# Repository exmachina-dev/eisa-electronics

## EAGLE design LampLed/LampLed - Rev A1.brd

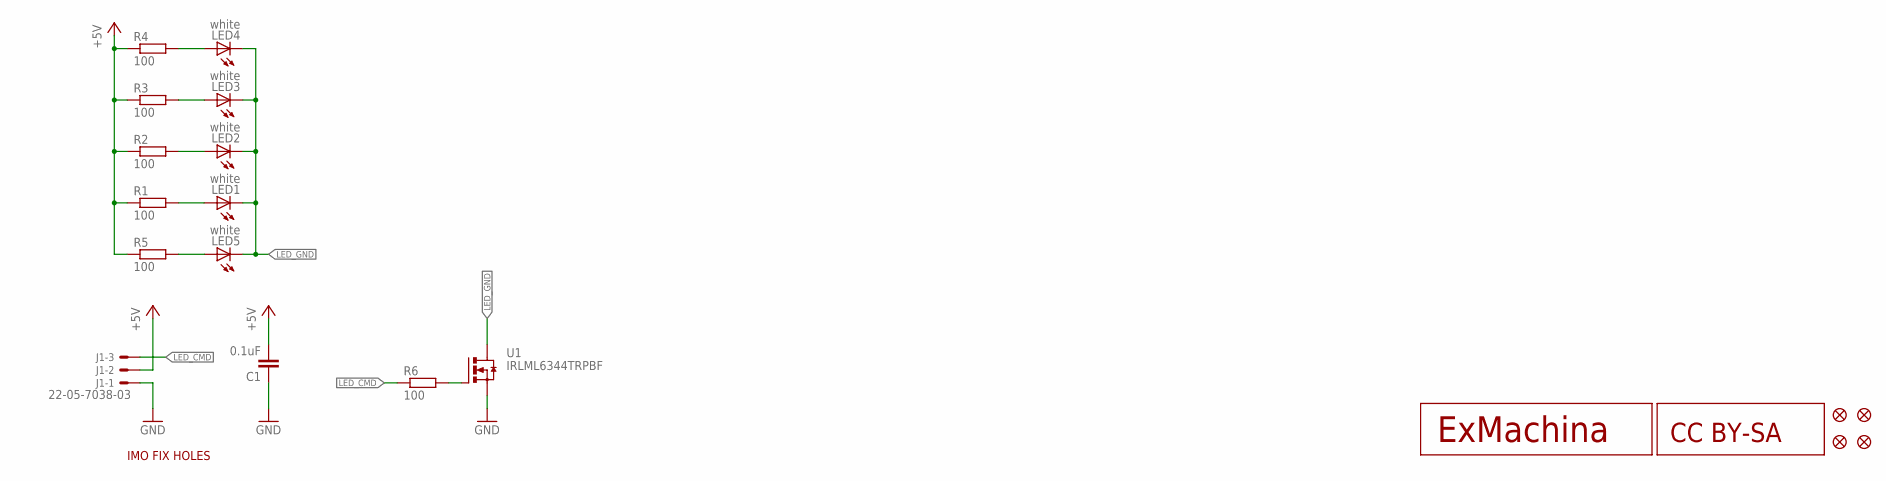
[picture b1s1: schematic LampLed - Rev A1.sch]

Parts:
C1: 0.1uF; C0603
J1: 22-05-7038-03; 7395-03
JP1, JP2, JP3, JP4: FIDUCIAL1X2; FIDUCIAL-1X2
LED1, LED2, LED3, LED4, LED5: white; CHIP-LED0603
R1, R2, R3, R4, R5, R6: 100; R0603
U1: IRLML6344TRPBF; SOT95P240X112-3N
U$1: IMO-FIXHOLES
U$2: EXMACHINA-LOGO-NAME; EXM-LOGO-BASELINE
U$3: CC-BY-SA

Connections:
+5V: C1.2, J1.2, R1.1, R2.1, R3.1, R4.1, R5.1
GND: C1.1, J1.1, U1.2 (S)
LED_CMD: J1.3, R6.1
LED_GND: LED1.C, LED2.C, LED3.C, LED4.C, LED5.C, U1.3 (D)
unnamed: LED1.A, R1.2
unnamed: LED2.A, R2.2
unnamed: LED3.A, R3.2
unnamed: LED4.A, R4.2
unnamed: LED5.A, R5.2
unnamed: R6.2, U1.1 (G)

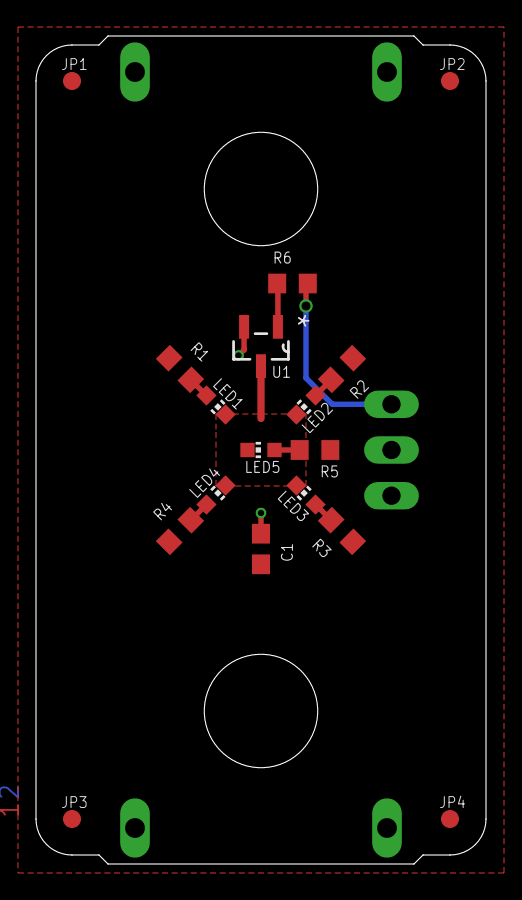
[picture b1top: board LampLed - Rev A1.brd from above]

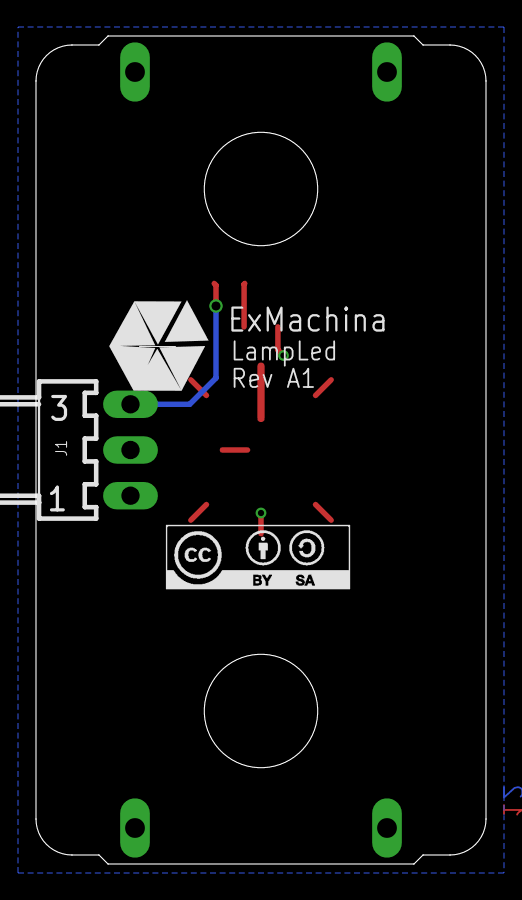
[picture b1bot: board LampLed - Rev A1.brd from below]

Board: 2 copper layers, 25.0 x 46.0 mm, 21 parts (3 on the bottom side), 10 nets.

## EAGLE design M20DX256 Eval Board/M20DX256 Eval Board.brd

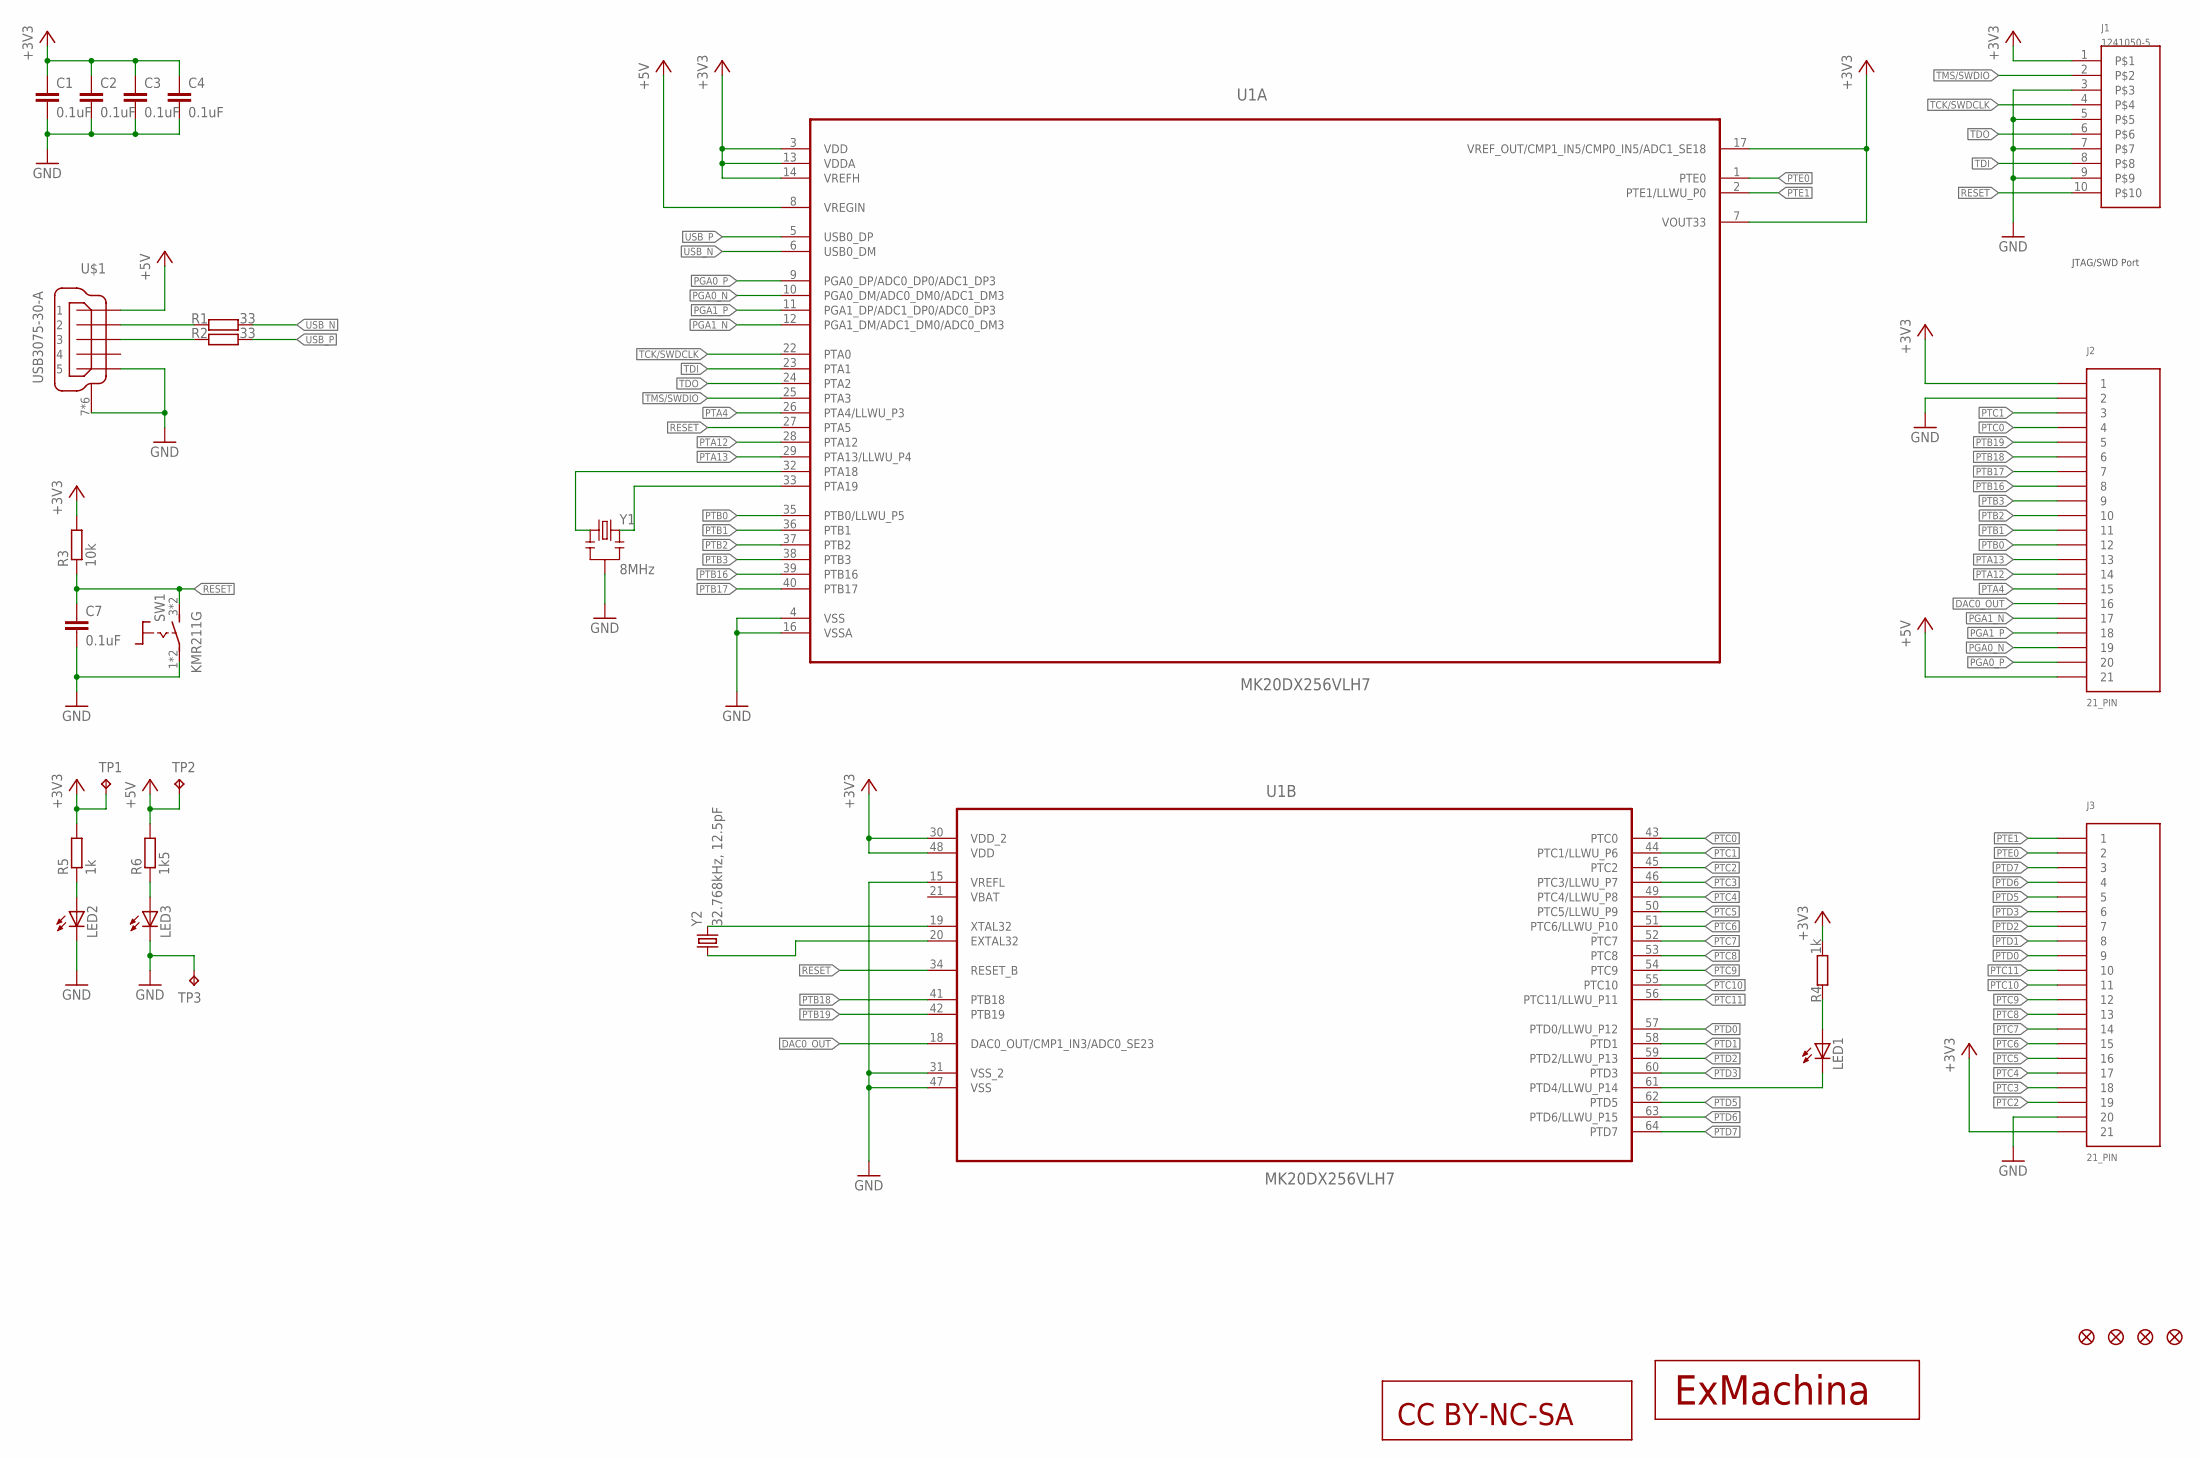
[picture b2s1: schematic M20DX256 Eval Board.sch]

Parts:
C1, C2, C3, C4, C7: 0.1uF; C0603; MPN MC0603B104K160CT
J1: 1241050-5; 2.54/2X5; MPN 1241050-5
J2, J3: 21_PIN; 21_CUSTOM
JP1, JP2, JP3, JP4: FIDUCIAL1X2; FIDUCIAL-1X2
LED1, LED2, LED3: LEDCHIP-LED0603; CHIP-LED0603
R1, R2: 33; R0603; MPN MCMR06X33R0FTL
R3: 10k; R0603; MPN MCMR06X1002FTL
R4, R5: 1k; R0603; MPN MCMR06X1001FTL
R6: 1k5; R0603; MPN MCMR06X1501FTL
SW1: KMR211G; KM_SERIE; MPN KMR211G LFS
TP1, TP2, TP3: TPB1,27; B1,27
U1: MK20DX256VLH7; QFP50P1200X1200X160-64N
U$1: USB3075-30-A; USB_MICROB_SMT; MPN USB3075-30-A
U$3: EXMACHINA-LOGO-NAME; EXM-LOGO-BASELINE
U$4: CC-BY-NC-SA
Y1: 8MHz; RESONATOR-SMD; MPN CSTCE8M00G55Z-R0
Y2: 32.768kHz, 12.5pF; ABS07; MPN ABS07-32.768KHZ-1-T

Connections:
+3V3: C1.1, C2.1, C3.1, C4.1, J1.1, J2.P$1 (1), J3.P$21 (21), R3.2, R4.2, R5.2, TP1.TP, U1.3 (VDD), U1.7 (VOUT33), U1.13 (VDDA), U1.14 (VREFH), U1.17 (VREF_OUT/CMP1_IN5/CMP0_IN5/ADC1_SE18), U1.30 (VDD_2), U1.48 (VDD)
+5V: J2.P$21 (21), R6.2, TP2.TP, U1.8 (VREGIN), U$1.1
DAC0_OUT: J2.P$16 (16), U1.18 (DAC0_OUT/CMP1_IN3/ADC0_SE23)
GND: C1.2, C2.2, C3.2, C4.2, C7.2, J1.3, J1.5, J1.7, J1.9, J2.P$2 (2), J3.P$20 (20), LED2.C, LED3.C, SW1.1 (2), SW1.2, TP3.TP, U1.4 (VSS), U1.15 (VREFL), U1.16 (VSSA), U1.31 (VSS_2), U1.47 (VSS), U$1.5, U$1.7 (S), U$1.8 (S), U$1.9 (S), U$1.10 (S), U$1.11 (S), U$1.12 (S), Y1.2
unnamed: R1.1, U$1.2
unnamed: R2.1, U$1.3
unnamed: U1.33 (PTA19), Y1.3
unnamed: U1.32 (PTA18), Y1.1
unnamed: U1.19 (XTAL32), Y2.2
unnamed: U1.20 (EXTAL32), Y2.1
unnamed: LED1.C, U1.61 (PTD4/LLWU_P14)
unnamed: LED1.A, R4.1
unnamed: LED3.A, R6.1
unnamed: LED2.A, R5.1
PGA0_N: J2.P$19 (19), U1.10 (PGA0_DM/ADC0_DM0/ADC1_DM3)
PGA0_P: J2.P$20 (20), U1.9 (PGA0_DP/ADC0_DP0/ADC1_DP3)
PGA1_N: J2.P$17 (17), U1.12 (PGA1_DM/ADC1_DM0/ADC0_DM3)
PGA1_P: J2.P$18 (18), U1.11 (PGA1_DP/ADC1_DP0/ADC0_DP3)
PTA4: J2.P$15 (15), U1.26 (PTA4/LLWU_P3)
PTA12: J2.P$14 (14), U1.28 (PTA12)
PTA13: J2.P$13 (13), U1.29 (PTA13/LLWU_P4)
PTB0: J2.P$12 (12), U1.35 (PTB0/LLWU_P5)
PTB1: J2.P$11 (11), U1.36 (PTB1)
PTB2: J2.P$10 (10), U1.37 (PTB2)
PTB3: J2.P$9 (9), U1.38 (PTB3)
PTB16: J2.P$8 (8), U1.39 (PTB16)
PTB17: J2.P$7 (7), U1.40 (PTB17)
PTB18: J2.P$6 (6), U1.41 (PTB18)
PTB19: J2.P$5 (5), U1.42 (PTB19)
PTC0: J2.P$4 (4), U1.43 (PTC0)
PTC1: J2.P$3 (3), U1.44 (PTC1/LLWU_P6)
PTC2: J3.P$19 (19), U1.45 (PTC2)
PTC3: J3.P$18 (18), U1.46 (PTC3/LLWU_P7)
PTC4: J3.P$17 (17), U1.49 (PTC4/LLWU_P8)
PTC5: J3.P$16 (16), U1.50 (PTC5/LLWU_P9)
PTC6: J3.P$15 (15), U1.51 (PTC6/LLWU_P10)
PTC7: J3.P$14 (14), U1.52 (PTC7)
PTC8: J3.P$13 (13), U1.53 (PTC8)
PTC9: J3.P$12 (12), U1.54 (PTC9)
PTC10: J3.P$11 (11), U1.55 (PTC10)
PTC11: J3.P$10 (10), U1.56 (PTC11/LLWU_P11)
PTD0: J3.P$9 (9), U1.57 (PTD0/LLWU_P12)
PTD1: J3.P$8 (8), U1.58 (PTD1)
PTD2: J3.P$7 (7), U1.59 (PTD2/LLWU_P13)
PTD3: J3.P$6 (6), U1.60 (PTD3)
PTD5: J3.P$5 (5), U1.62 (PTD5)
PTD6: J3.P$4 (4), U1.63 (PTD6/LLWU_P15)
PTD7: J3.P$3 (3), U1.64 (PTD7)
PTE0: J3.P$2 (2), U1.1 (PTE0)
PTE1: J3.P$1 (1), U1.2 (PTE1/LLWU_P0)
RESET: C7.1, J1.10, R3.1, SW1.3 (1), SW1.4 (1), U1.27 (PTA5), U1.34 (RESET_B)
TCK/SWDCLK: J1.4, U1.22 (PTA0)
TDI: J1.8, U1.23 (PTA1)
TDO: J1.6, U1.24 (PTA2)
TMS/SWDIO: J1.2, U1.25 (PTA3)
USB_N: R1.2, U1.6 (USB0_DM)
USB_P: R2.2, U1.5 (USB0_DP)
VBAT: U1.21 (VBAT)

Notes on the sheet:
JTAG/SWD Port

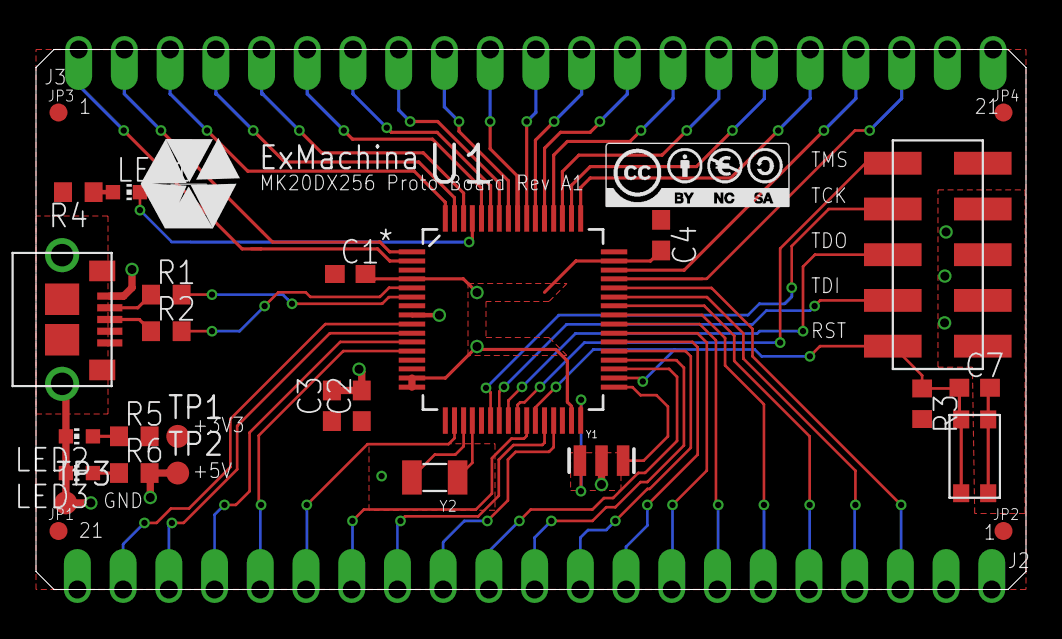
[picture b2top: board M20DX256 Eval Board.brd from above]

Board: 2 copper layers, 55.0 x 30.0 mm, 31 parts (0 on the bottom side), 57 nets.

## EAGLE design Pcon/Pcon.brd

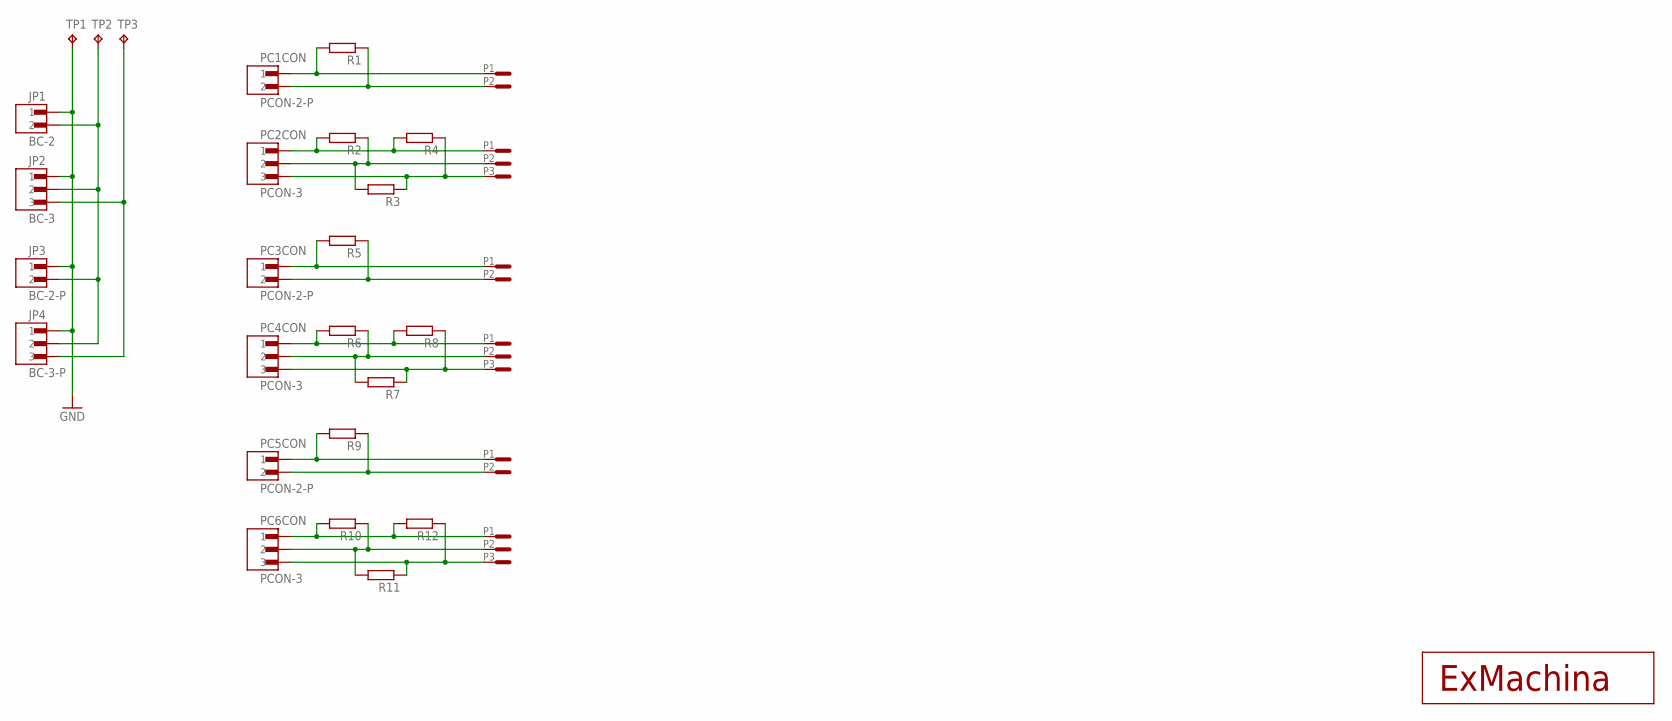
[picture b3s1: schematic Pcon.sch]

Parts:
JP1: BC-2
JP2: BC-3
JP3: BC-2-P
JP4: BC-3-P
PC1, PC3, PC5: PCON-2-P; PCON-2
PC2, PC4, PC6: PCON-3
R1, R2, R3, R4, R5, R6, R7, R8, R9, R10, R11, R12: R-EU_R0603; R0603
TP1, TP2, TP3: TPB1,27; B1,27
U$1: EXMACHINA-LOGO; EXM-LOGO

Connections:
GND: JP1.1, JP2.1, JP3.1, JP4.1, TP1.TP
unnamed: PC1.2, PC1.P2, R1.1
unnamed: PC1.1, PC1.P1, R1.2
unnamed: PC2.3, PC2.P3, R3.1, R4.1
unnamed: PC2.2, PC2.P2, R2.1, R3.2
unnamed: PC2.1, PC2.P1, R2.2, R4.2
unnamed: JP1.2, JP2.2, JP3.2, JP4.2, TP2.TP
unnamed: JP2.3, JP4.3, TP3.TP
unnamed: PC3.2, PC3.P2, R5.1
unnamed: PC3.1, PC3.P1, R5.2
unnamed: PC4.3, PC4.P3, R7.1, R8.1
unnamed: PC4.2, PC4.P2, R6.1, R7.2
unnamed: PC4.1, PC4.P1, R6.2, R8.2
unnamed: PC5.2, PC5.P2, R9.1
unnamed: PC5.1, PC5.P1, R9.2
unnamed: PC6.3, PC6.P3, R11.1, R12.1
unnamed: PC6.2, PC6.P2, R10.1, R11.2
unnamed: PC6.1, PC6.P1, R10.2, R12.2

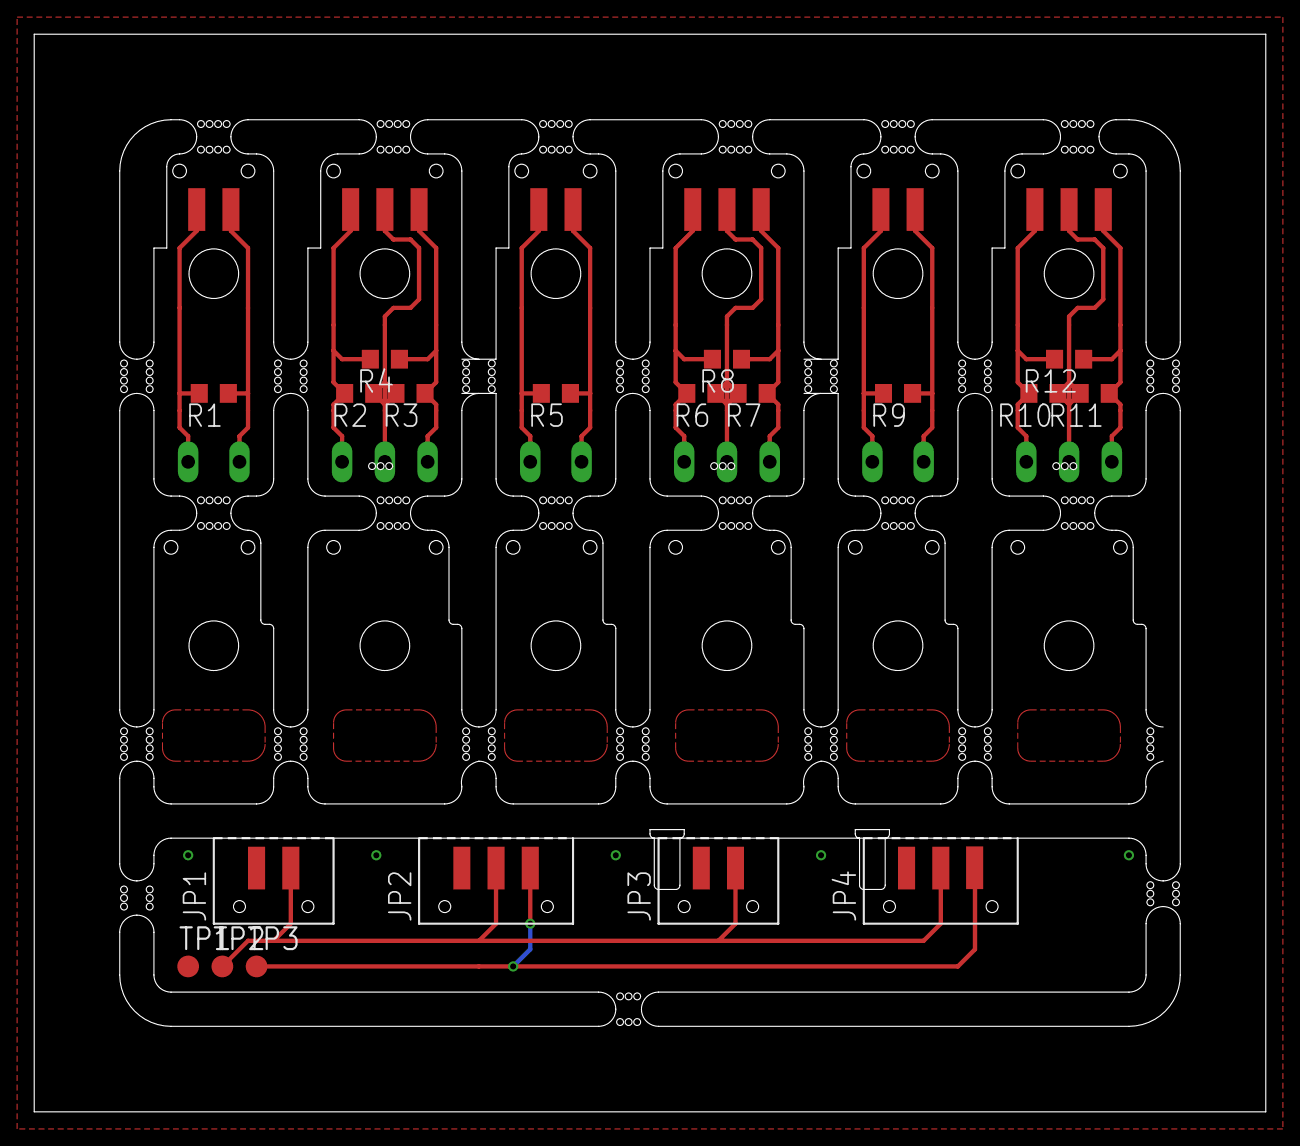
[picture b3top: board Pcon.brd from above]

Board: 2 copper layers, 72.0 x 63.0 mm, 26 parts (1 on the bottom side), 18 nets.

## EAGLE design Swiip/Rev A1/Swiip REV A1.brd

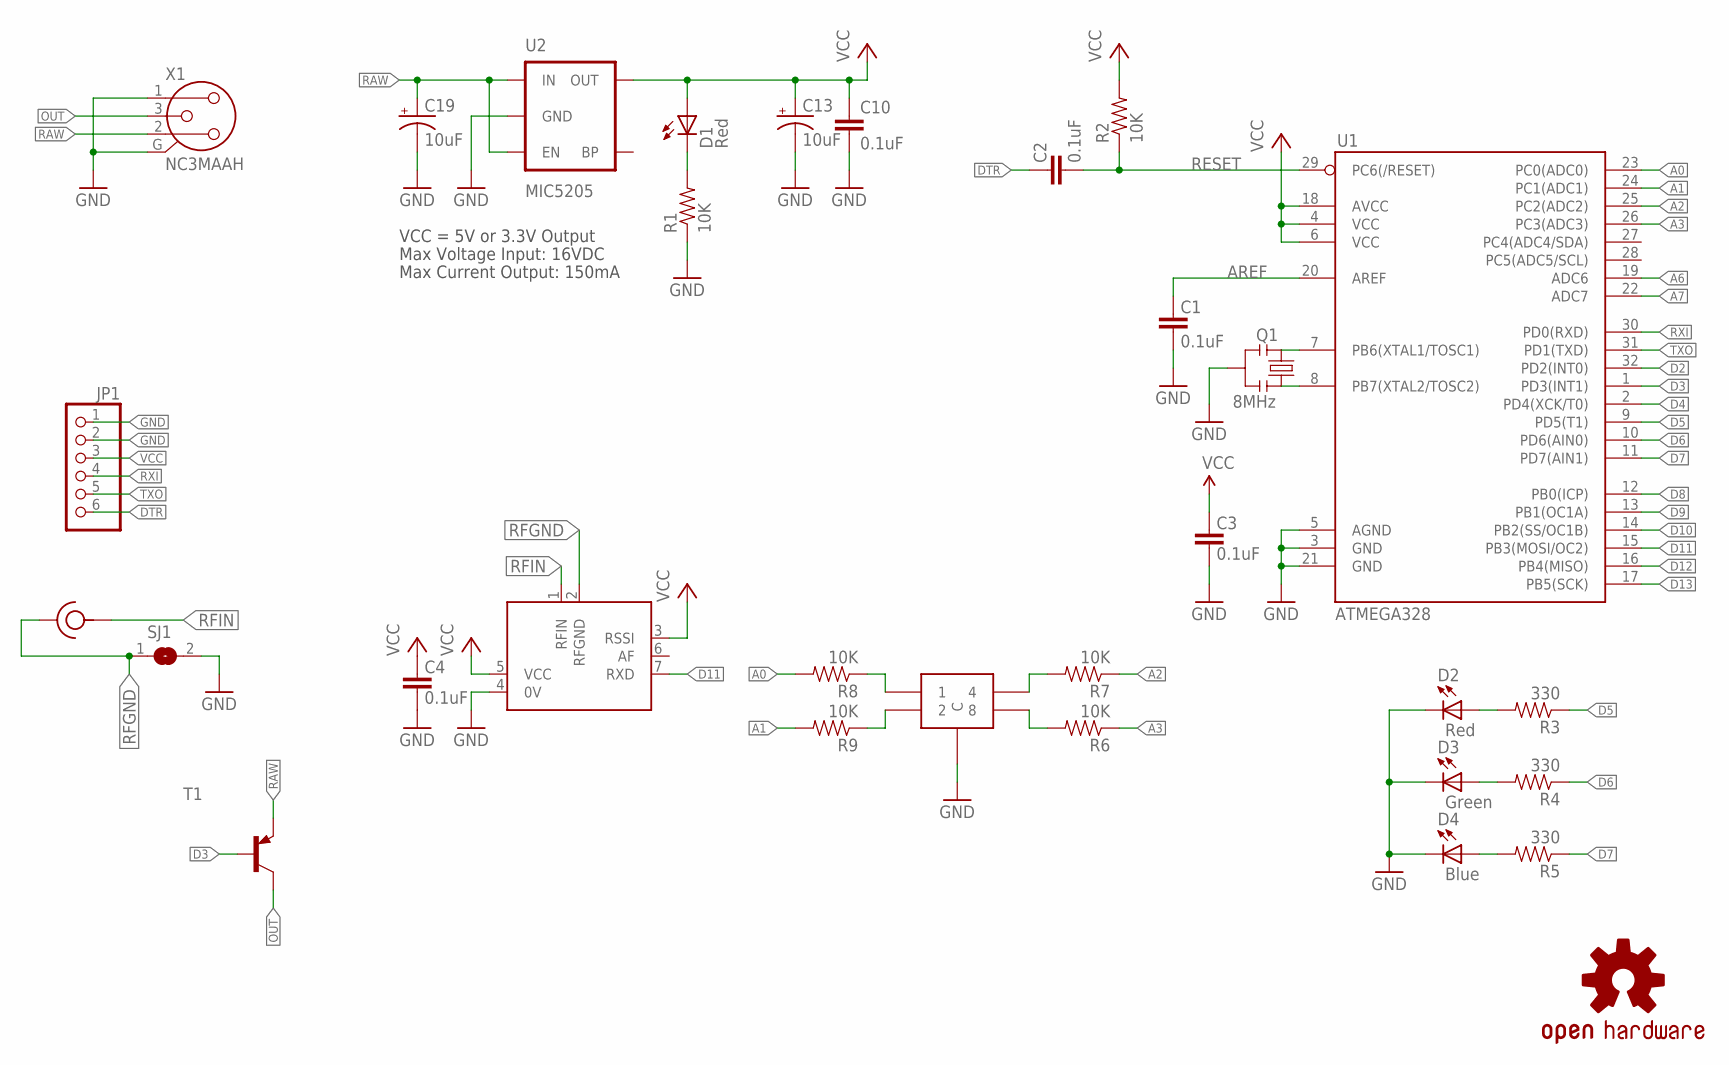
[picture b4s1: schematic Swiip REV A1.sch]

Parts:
C1, C2, C3, C4, C10: 0.1uF; 0603-CAP; MPN MC0603F104Z160CT
C13, C19: 10uF; EIA3216; MPN MCCTA106M006
D1: Red; 0603-LED-ALT1; MPN MCL-S290SRC
D2: Red; 0603-LED-ALT1; MPN 703-0109
D3: Green; 0603-LED-ALT1; MPN 703-0109
D4: Blue; 0603-LED-ALT1; MPN 703-0109
JP1: PINHD-1X6; 1X06; MPN MC34751
Q1: 8MHz; RESONATOR-SMD-1:1; MPN CSTCE8M00G55Z-R0
R1, R2, R6, R7, R8, R9: 10K; 0603-RES; MPN MCHP03W8F1002T5E
R3, R4, R5: 330; 0603-RES; MPN MCWR06X3300FTL
RF1: 132203; MPN 132203
SJ1: SJ
T1: -PNP-SOT23-BCE; SOT23-BCE; MPN BC807-25
U1: ATMEGA328; TQFP32-08; MPN ATMEGA328-AUR
U2: MIC5205; SOT23-5; MPN MIC5205-3.0YM5 TR
U$1: PT65-101-L508; MPN PT65-101-L508
U$2: RX2A-433-64; RX2A; MPN RX2A-433-64
U$3: OSHW-LOGOS; OSHW-LOGO-S
X1: NC3MAAH; NC3MAH; MPN NC3MAAH

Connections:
A0: R8.2, U1.23 (PC0(ADC0))
A1: R9.2, U1.24 (PC1(ADC1))
A2: R7.1, U1.25 (PC2(ADC2))
A3: R6.1, U1.26 (PC3(ADC3))
A6: U1.19 (ADC6)
A7: U1.22 (ADC7)
AREF: C1.2, U1.20 (AREF)
D2: U1.32 (PD2(INT0))
D3: T1.B, U1.1 (PD3(INT1))
D4: U1.2 (PD4(XCK/T0))
D5: R3.1, U1.9 (PD5(T1))
D6: R4.1, U1.10 (PD6(AIN0))
D7: R5.1, U1.11 (PD7(AIN1))
D8: U1.12 (PB0(ICP))
D9: U1.13 (PB1(OC1A))
D10: U1.14 (PB2(SS/OC1B))
D11: U1.15 (PB3(MOSI/OC2)), U$2.7 (RXD)
D12: U1.16 (PB4(MISO))
D13: U1.17 (PB5(SCK))
DTR: C2.2, JP1.6
GND: C1.1, C3.1, C4.1, C10.2, C13.C (-), C19.C (-), D2.C, D3.C, D4.C, JP1.1, JP1.2, Q1.2, R1.1, SJ1.2, U1.3 (GND), U1.5 (AGND), U1.21 (GND), U2.2 (GND), U$1.C1 (C), U$1.C2 (C), U$2.4 (0V), X1.1, X1.G
unnamed: Q1.3, U1.8 (PB7(XTAL2/TOSC2))
unnamed: Q1.1, U1.7 (PB6(XTAL1/TOSC1))
unnamed: D3.A, R4.2
unnamed: D1.C, R1.2
unnamed: D4.A, R5.2
unnamed: R8.1, U$1.1
unnamed: D2.A, R3.2
unnamed: R9.1, U$1.2
unnamed: R7.2, U$1.4
unnamed: R6.2, U$1.8
OUT: T1.C, X1.3
RAW: C19.A (+), T1.E, U2.1 (IN), U2.3 (EN), X1.2
RESET: C2.1, R2.1, U1.29 (PC6(/RESET))
RFGND: RF1.G1 (GND), RF1.G2 (GND), RF1.G3 (GND), RF1.G4 (GND), SJ1.1, U$2.2 (RFGND)
RFIN: RF1.P (RF), U$2.1 (RFIN)
RXI: JP1.4, U1.30 (PD0(RXD))
TXO: JP1.5, U1.31 (PD1(TXD))
VCC: C3.2, C4.2, C10.1, C13.A (+), D1.A, JP1.3, R2.2, U1.4 (VCC), U1.6 (VCC), U1.18 (AVCC), U2.5 (OUT), U$2.3 (RSSI), U$2.5 (VCC)

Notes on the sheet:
Max Voltage Input: 16VDC
Max Current Output: 150mA
VCC = 5V or 3.3V Output

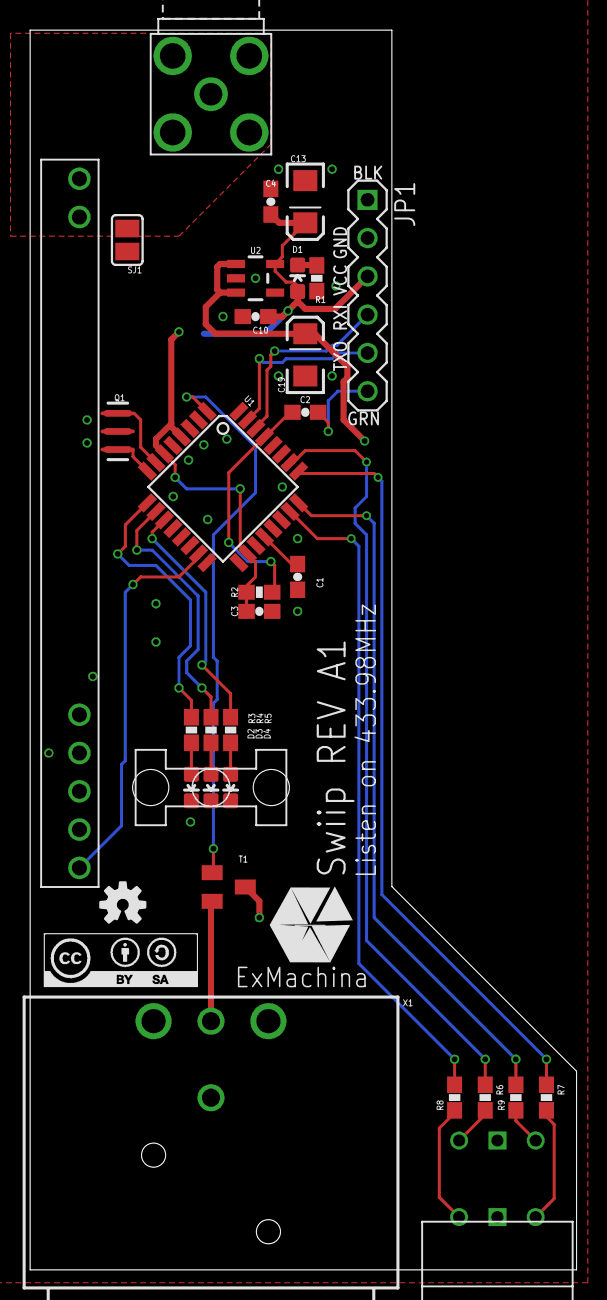
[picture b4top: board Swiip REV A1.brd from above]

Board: 2 copper layers, 36.2 x 82.2 mm, 34 parts (0 on the bottom side), 30 nets.

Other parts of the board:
U$4: CC-BY-SA
U$5: 1275.100
U$6: EXM-LOGO

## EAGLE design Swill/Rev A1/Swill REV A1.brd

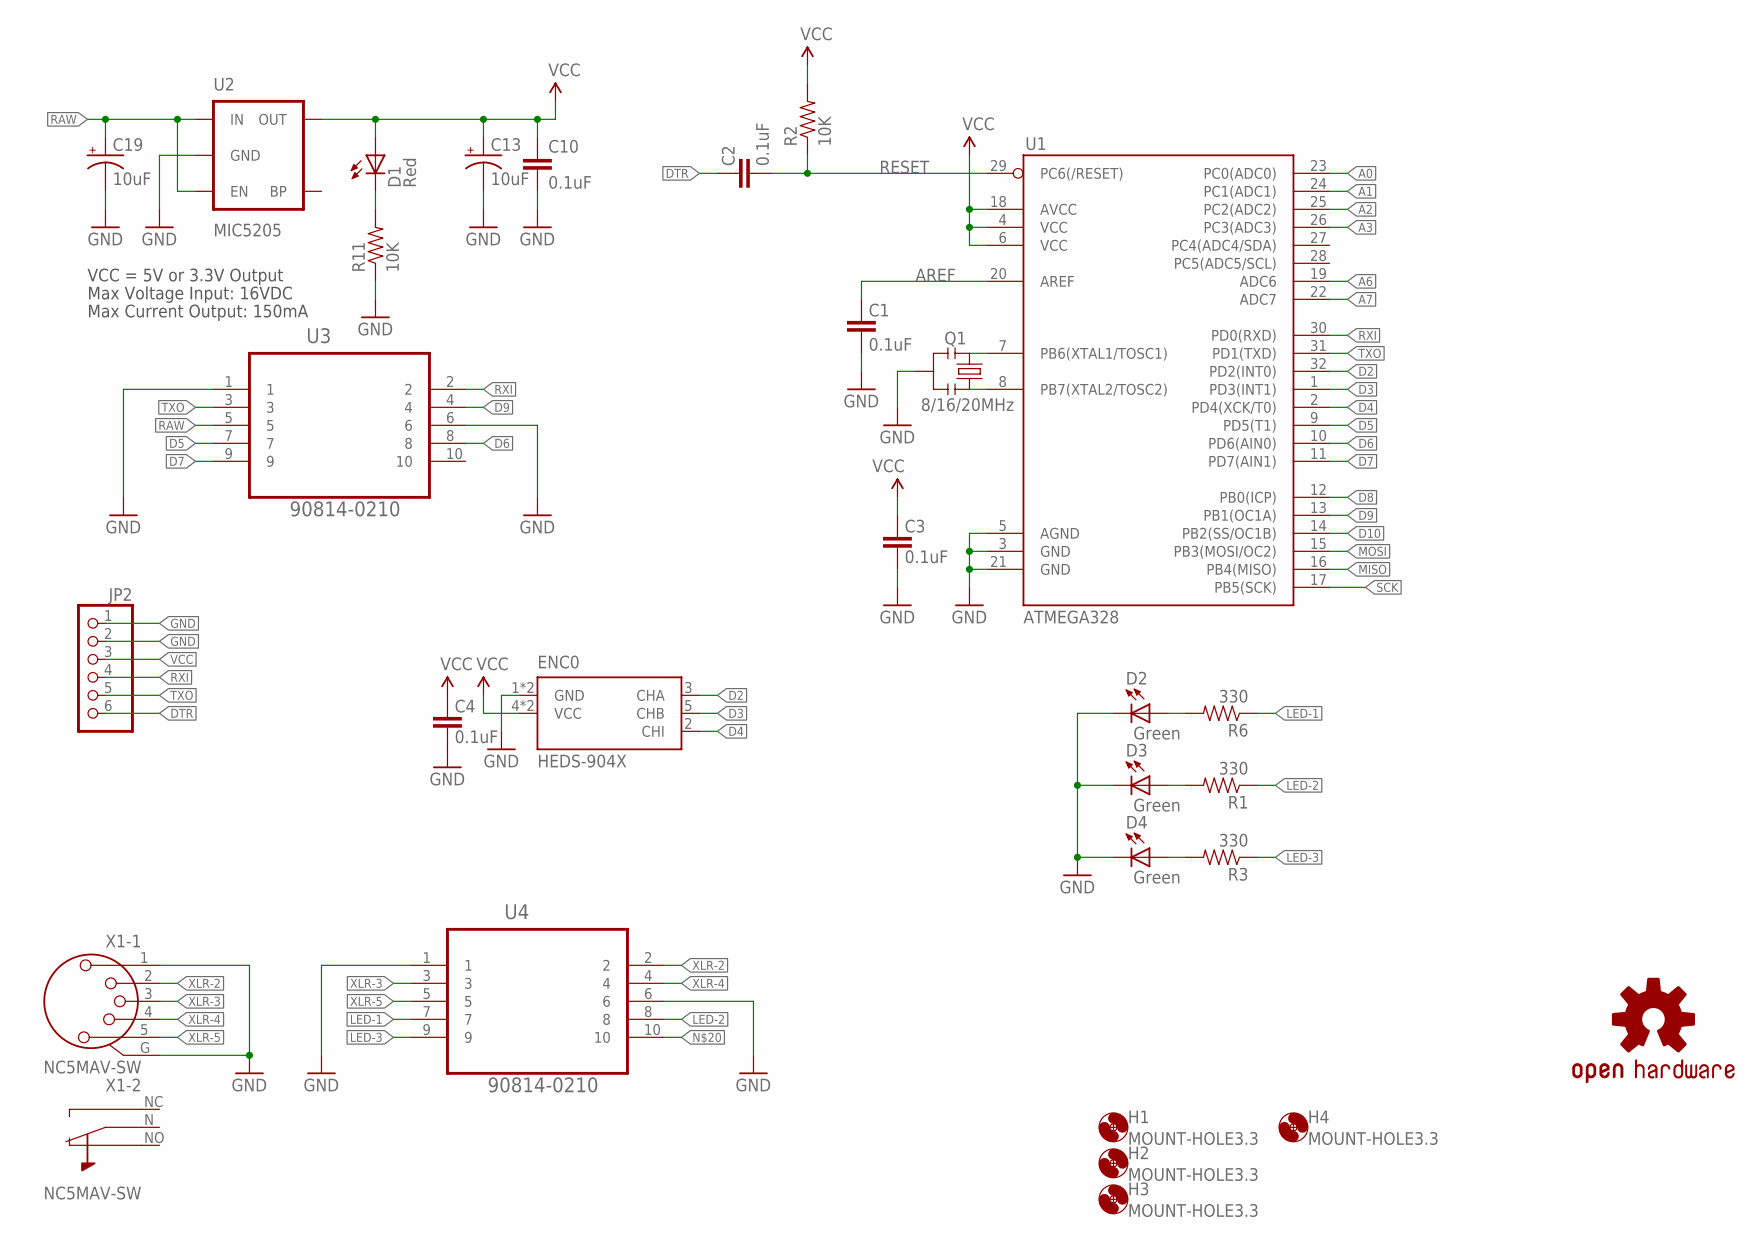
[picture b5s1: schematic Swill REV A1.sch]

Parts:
C1, C2, C3, C4, C10: 0.1uF; 0603-CAP; MPN MC0603F104Z160CT
C13, C19: 10uF; EIA3216; MPN MCCTA106M006
D1: Red; 0603-LED-ALT1; MPN MCL-S290SRC
D2, D3, D4: Green; 0603-LED-ALT1; MPN 703-0109
ENC0: HEDS-904X; HEDS-9041; MPN HEDS-9040#J00
H1, H2, H3, H4: MOUNT-HOLE3.3; 3,3
JP2: PINHD-1X6; 1X06; MPN MC34751
Q1: 8/16/20MHz; RESONATOR-SMD-1:1; MPN CSTCE8M00G55Z-R0
R1, R3, R6: 330; 0603-RES; MPN MCWR06X3300FTL
R2, R11: 10K; 0603-RES; MPN MCHP03W8F1002T5E
U1: ATMEGA328; TQFP32-08; MPN ATMEGA328-AUR
U2: MIC5205; SOT23-5; MPN MIC5205-3.0YM5 TR
U3, U4: 90814-0210; MOLEX_90814-0210
U$3: OSHW-LOGOS; OSHW-LOGO-S
X1: NC5MAV-SW

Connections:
3.3V: C4.2
A0: U1.23 (PC0(ADC0))
A1: U1.24 (PC1(ADC1))
A2: U1.25 (PC2(ADC2))
A3: U1.26 (PC3(ADC3))
A6: U1.19 (ADC6)
A7: U1.22 (ADC7)
AREF: C1.2, U1.20 (AREF)
D2: ENC0.3 (CHA), U1.32 (PD2(INT0))
D3: ENC0.5 (CHB), U1.1 (PD3(INT1))
D4: ENC0.2 (CHI), U1.2 (PD4(XCK/T0))
D5: U1.9 (PD5(T1)), U3.7
D6: U1.10 (PD6(AIN0)), U3.8
D7: U1.11 (PD7(AIN1)), U3.9
D8: U1.12 (PB0(ICP))
D9: U1.13 (PB1(OC1A)), U3.4
D10: U1.14 (PB2(SS/OC1B))
DTR: C2.2, JP2.6
GND: C1.1, C3.1, C4.1, C10.2, C13.C (-), C19.C (-), D2.C, D3.C, D4.C, ENC0.1 (GND), ENC0.A (GND), JP2.1, JP2.2, Q1.2, R11.1, U1.3 (GND), U1.5 (AGND), U1.21 (GND), U2.2 (GND), U3.1, U3.6, U4.1, U4.6, X1.1, X1.G
LED-1: R6.1, U4.7
LED-2: R1.1, U4.8
LED-3: R3.1, U4.9
MISO: U1.16 (PB4(MISO))
MOSI: U1.15 (PB3(MOSI/OC2))
unnamed: Q1.3, U1.8 (PB7(XTAL2/TOSC2))
unnamed: Q1.1, U1.7 (PB6(XTAL1/TOSC1))
unnamed: D3.A, R1.2
unnamed: D1.C, R11.2
unnamed: D4.A, R3.2
unnamed: D2.A, R6.2
RAW: C19.A (+), U2.1 (IN), U2.3 (EN), U3.5
RESET: C2.1, R2.1, U1.29 (PC6(/RESET))
RXI: JP2.4, U1.30 (PD0(RXD)), U3.2
SCK: U1.17 (PB5(SCK))
TXO: JP2.5, U1.31 (PD1(TXD)), U3.3
VCC: C3.2, C10.1, C13.A (+), D1.A, ENC0.4 (VCC), ENC0.B (VCC), JP2.3, R2.2, U1.4 (VCC), U1.6 (VCC), U1.18 (AVCC), U2.5 (OUT)
XLR-2: U4.2, X1.2
XLR-3: U4.3, X1.3
XLR-4: U4.4, X1.4
XLR-5: U4.5, X1.5

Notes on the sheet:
Max Voltage Input: 16VDC
Max Current Output: 150mA
VCC = 5V or 3.3V Output

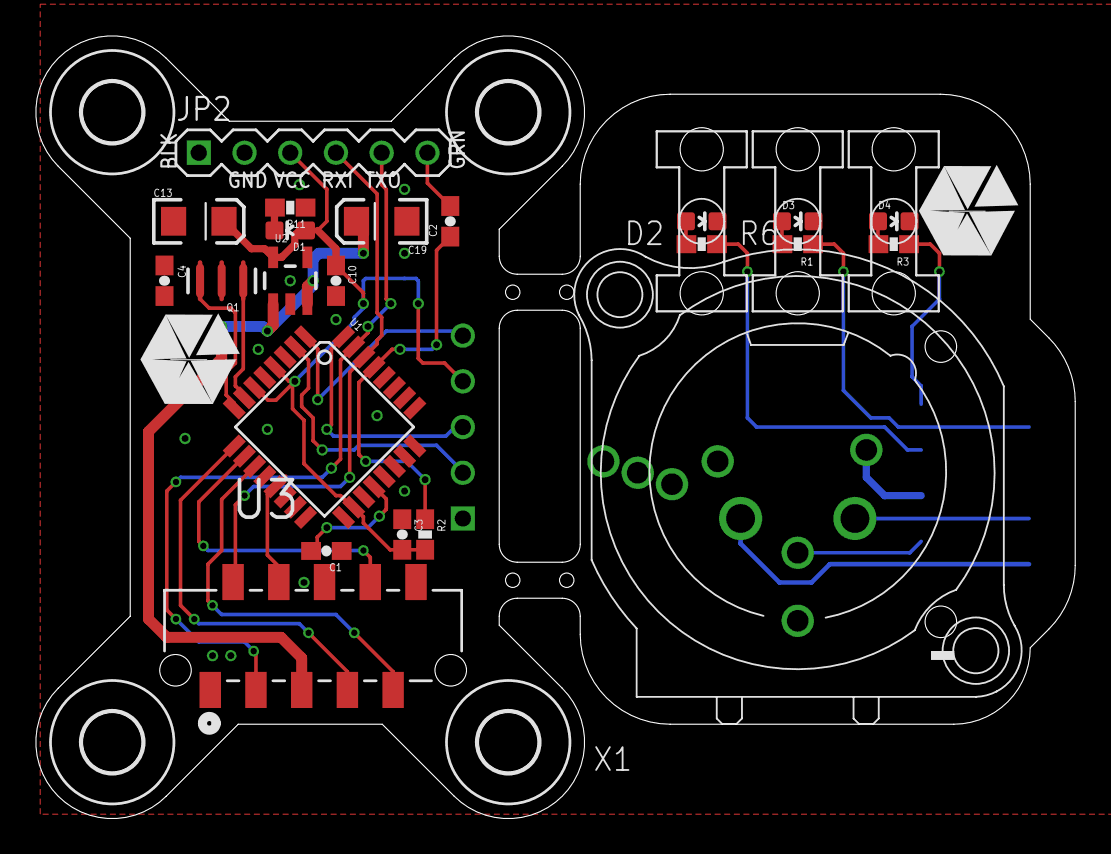
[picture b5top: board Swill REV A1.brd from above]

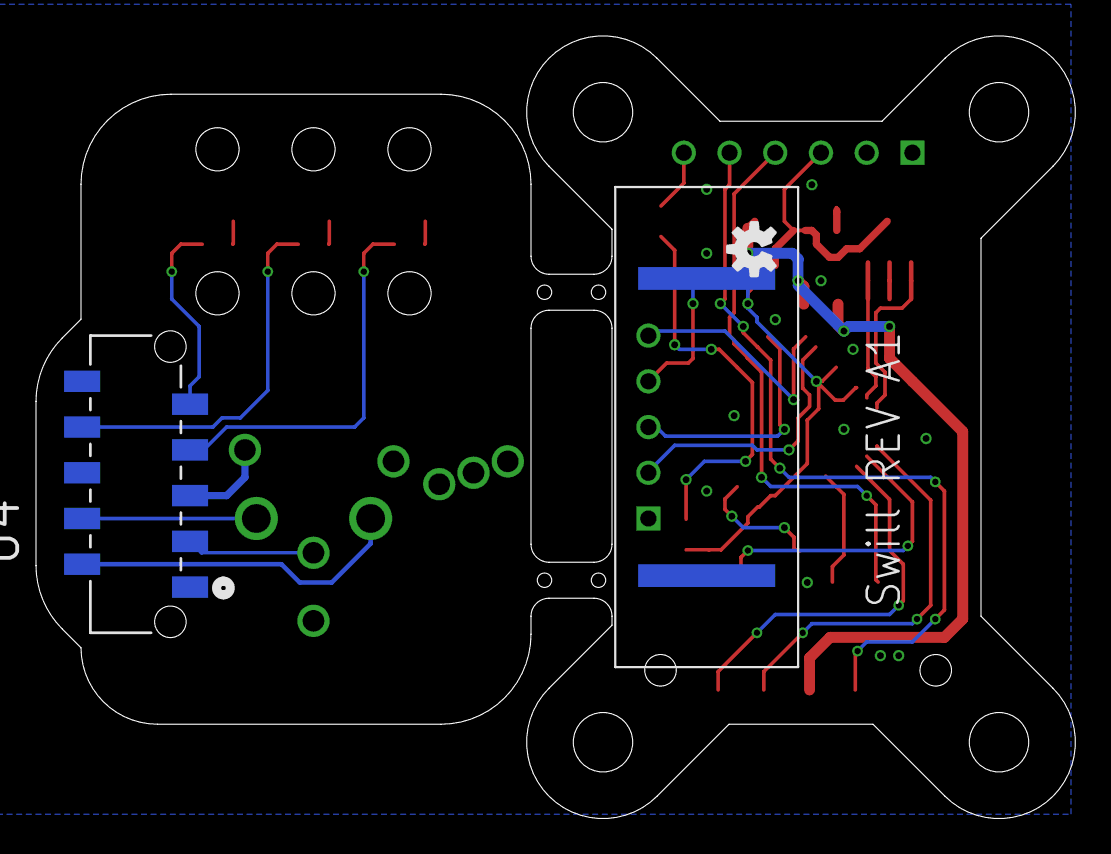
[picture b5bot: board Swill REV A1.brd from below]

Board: 2 copper layers, 57.7 x 43.5 mm, 34 parts (3 on the bottom side), 28 nets.

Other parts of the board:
E$1, E$2: EXM-LOGO
U$4, U$5, U$6: 1275.100

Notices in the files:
Swiip/Rev A1/Swiip REV A1.brd:
Released under the Creative Commons Attribution Share-Alike 3.0 License
http://creativecommons.org/licenses/by-sa/3.0
